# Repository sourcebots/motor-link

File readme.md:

## MotorLink

A PCB for converting the wire solder terminals on the 12v geared motors into camblock or screw terminals.

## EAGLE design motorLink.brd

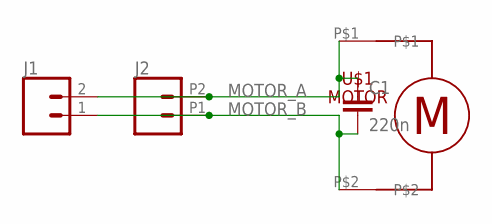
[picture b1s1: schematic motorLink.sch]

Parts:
C1: 220n; 1210
J1: CONN_025MM; SCREWTERMINAL-5MM-2
J2: CONN_022.54MM_SCREWTERM; 1X02_2.54_SCREWTERM
U$1: MOTOR

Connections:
MOTOR_A: C1.1, J1.2, J2.P2 (2), U$1.P$1
MOTOR_B: C1.2, J1.1, J2.P1 (1), U$1.P$2

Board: 2 copper layers, 4 parts (1 on the bottom side), 2 nets, no tracks yet.

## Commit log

2018-06-05 Added initial board layout and gitignore
2018-06-05 Added readme
2018-06-30 Small changes
    Added top copper pours
    Cleaned up silkscreen

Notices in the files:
parts and their libraries:
SparkFun-Connectors: Licensing: Creative Commons ShareAlike 4.0 International - https://creativecommons.org/licenses/by-sa/4.0
SparkFun: Licensing: CC v3.0 Share-Alike You are welcome to use this library for commercial purposes.
